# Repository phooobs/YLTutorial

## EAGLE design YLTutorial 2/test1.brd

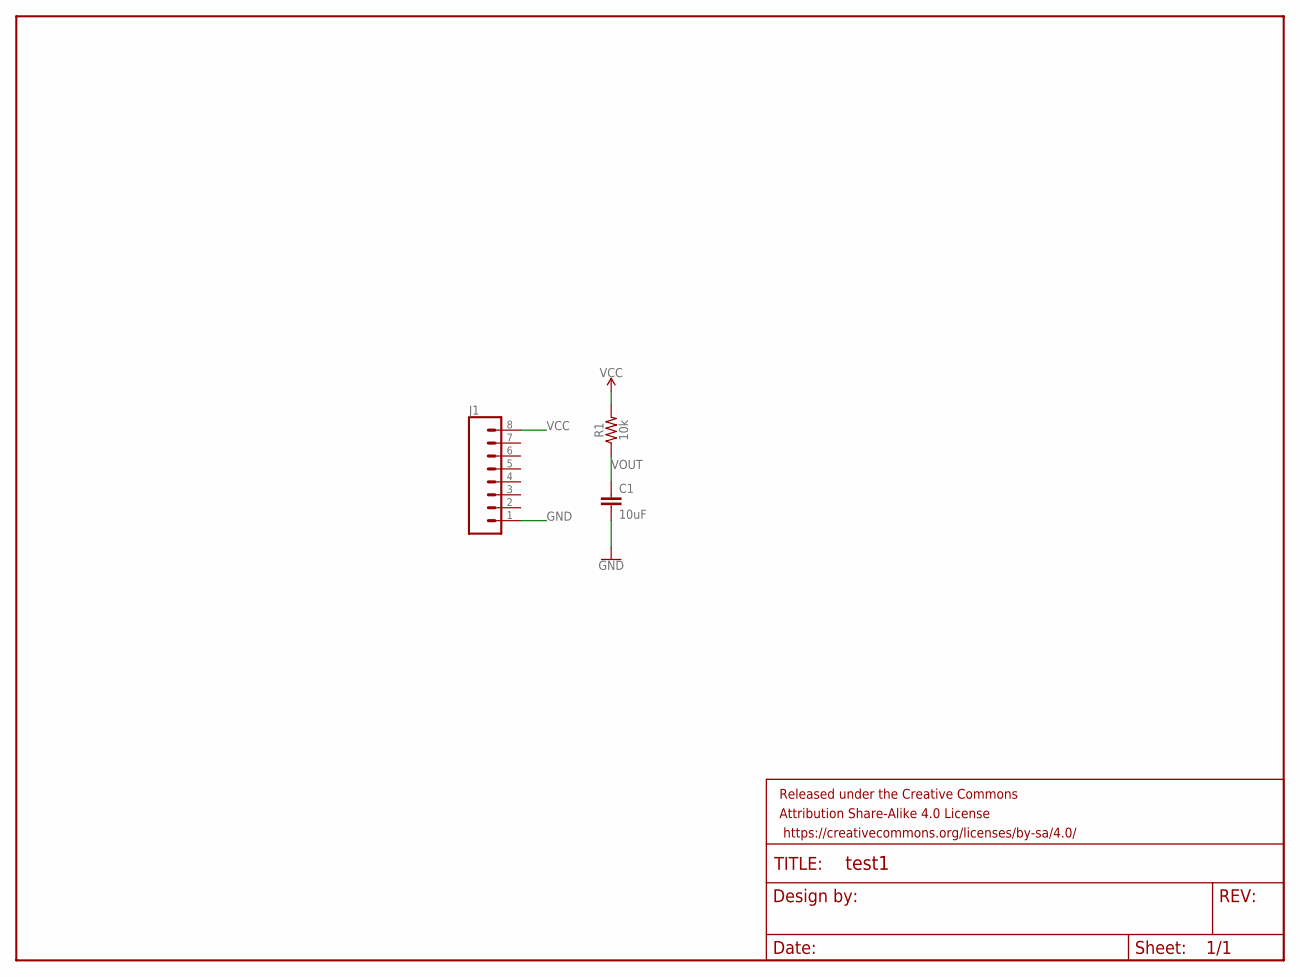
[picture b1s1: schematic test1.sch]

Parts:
C1: 10uF; CAP-PTH-SMALL-KIT
FRAME1: FRAME-LETTER; CREATIVE_COMMONS
J1: CONN_08"; 1X08
R1: 10k; 0805

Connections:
GND: C1.2, J1.1
VCC: J1.8, R1.2
VOUT: C1.1, R1.1

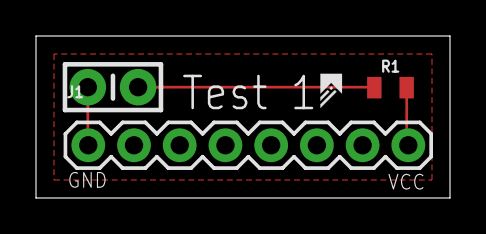
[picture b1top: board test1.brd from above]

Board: 2 copper layers, 23.0 x 9.0 mm, 4 parts (0 on the bottom side), 3 nets.

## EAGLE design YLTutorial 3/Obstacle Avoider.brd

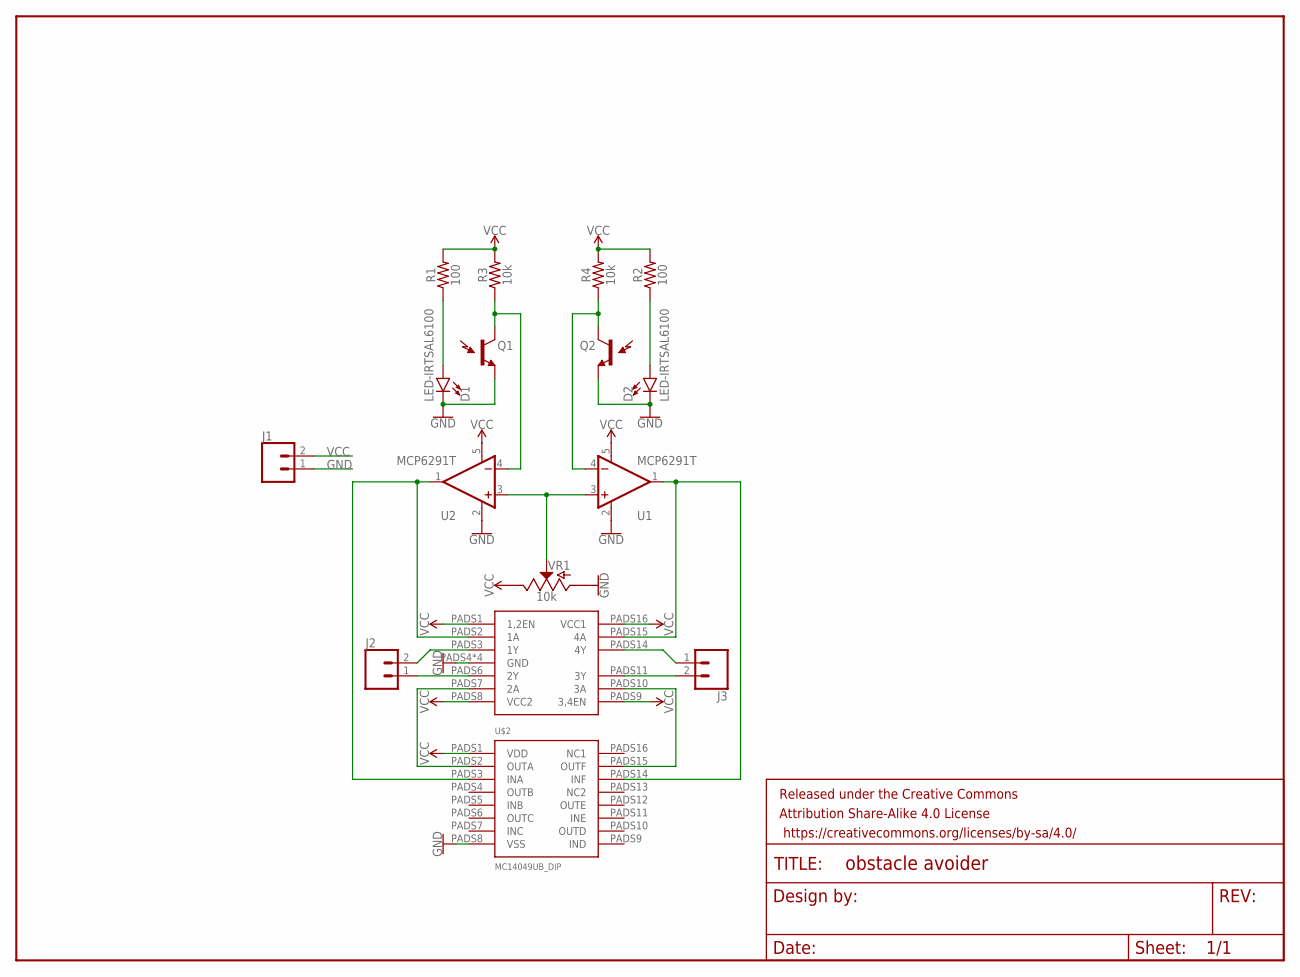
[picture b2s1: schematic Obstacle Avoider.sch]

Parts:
D1, D2: LED-IRTSAL6100; LED_5MM
FRAME1: FRAME-LETTER; CREATIVE_COMMONS
J1, J2, J3: CONN_02; 1X02
Q1, Q2: LTR-301
R1, R2: 100; AXIAL-0.3
R3, R4: 10k; AXIAL-0.3
U1, U2: MCP6291T; SOT23-5
U$1: L293DNE
U$2: MC14049UB_DIP
VR1: 10k; POT-PTH-ALPS-KIT

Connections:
GND: D1.K (C), D2.K (C), J1.1, Q1.E (E1), Q2.E (E1), U1.2 (V-), U2.2 (V-), U$1.PADS4 (GND), U$1.PADS5 (GND), U$1.PADS12 (GND), U$1.PADS13 (GND), U$2.PADS8 (VSS), VR1.P$3 (A)
unnamed: D1.A, R1.P$1 (1)
unnamed: D2.A, R2.P$1 (1)
unnamed: U2.1 (OUT), U$1.PADS2 (1A), U$2.PADS3 (INA)
unnamed: Q2.C (C1), R4.P$1 (1), U1.4 (-IN)
unnamed: U1.3 (+IN), U2.3 (+IN), VR1.P$2 (S)
unnamed: Q1.C (C1), R3.P$1 (1), U2.4 (-IN)
unnamed: U1.1 (OUT), U$1.PADS15 (4A), U$2.PADS14 (INF)
unnamed: U$1.PADS10 (3A), U$2.PADS15 (OUTF)
unnamed: J2.1, U$1.PADS6 (2Y)
unnamed: U$1.PADS7 (2A), U$2.PADS2 (OUTA)
unnamed: J2.2, U$1.PADS3 (1Y)
unnamed: J3.2, U$1.PADS11 (3Y)
unnamed: J3.1, U$1.PADS14 (4Y)
VCC: J1.2, R1.P$2 (2), R2.P$2 (2), R3.P$2 (2), R4.P$2 (2), U1.5 (V+), U2.5 (V+), U$1.PADS1 (1,2EN), U$1.PADS8 (VCC2), U$1.PADS9 (3,4EN), U$1.PADS16 (VCC1), U$2.PADS1 (VDD), VR1.P$1 (E)

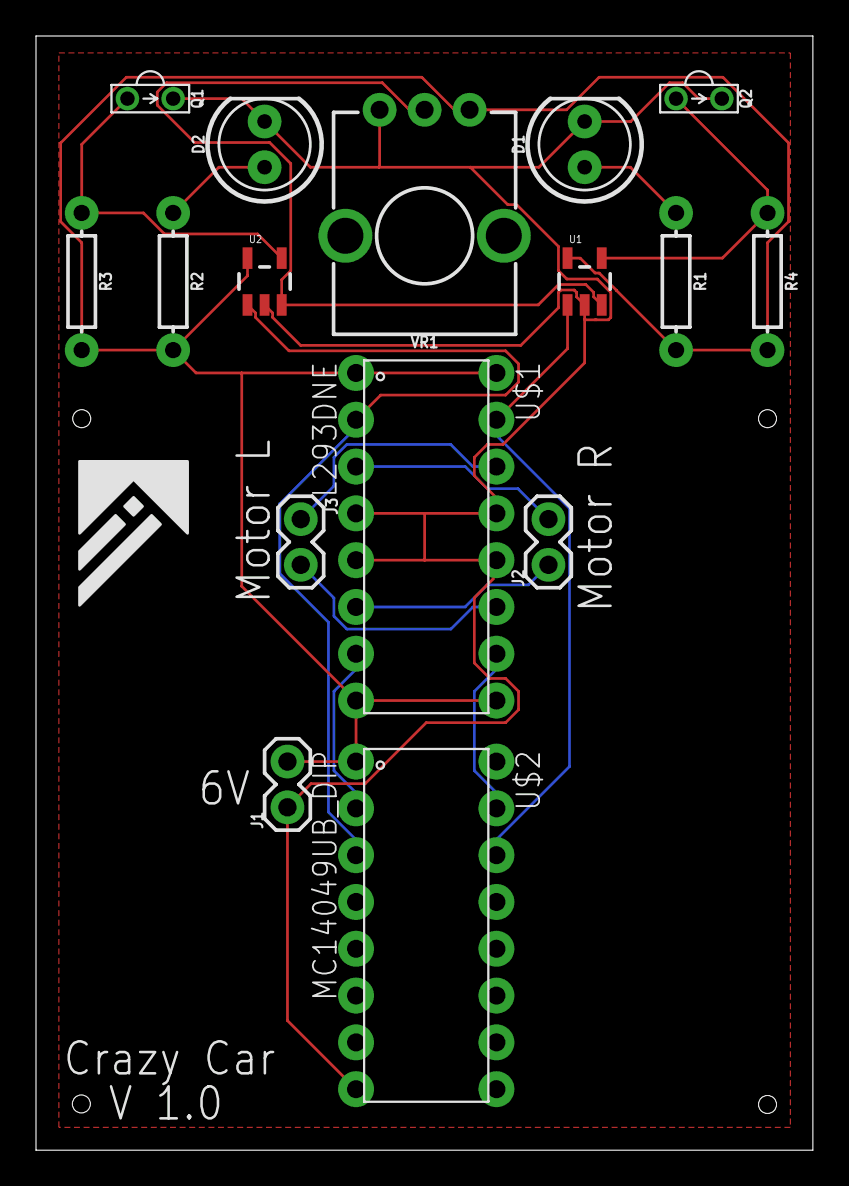
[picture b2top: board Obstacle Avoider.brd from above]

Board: 2 copper layers, 43.2 x 61.9 mm, 17 parts (0 on the bottom side), 15 nets.

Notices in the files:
parts and their libraries:
SparkFun-Aesthetics: Licensing: Creative Commons ShareAlike 4.0 International - https://creativecommons.org/licenses/by-sa/4.0
SparkFun-Aesthetics: Released under the Creative Commons Attribution Share-Alike 4.0 License
SparkFun-Aesthetics: https://creativecommons.org/licenses/by-sa/4.0
